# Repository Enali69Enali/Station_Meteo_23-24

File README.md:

# Station_Meteo_23-24
## Description du projet
Pour le cours de projet d'électronique lors de la 4e année du cycle d'ingénieur en alternance, celui ci réalise une girouette pour la station météo d'une ruche connectée. 
Une girouette est un objet de mesure pour nous donner la direction du vent. Ce projet reprend le projet Github 2022-2023 : [Station_Meteo_2022-2023](https://github.com/Solene49000/Station_Meteo_2022-2023). 
Dans ce projet, leur systeme de girouette n'était pas fonctionnelle, du à des differences de tensions trop faible par rapport au différente position de la fleche de la girouette. Nous proposons donc une solution alternative à ce probleme avec notre projet. 

Ce projet de station météo comporte plusieurs composants tels que:
- La quantité de pluie tombée 
- La vitesse du vent 
- La luminosité
- La température 
- L'humidité
Mais nous nous concentrons surtout sur la direction du vent avec la girouette. 

Pour voir la présentation du projet en cours, cliquez [ici](https://github.com/Enali69Enali/Station_Meteo_23-24/blob/master/rapport_de_s%C3%A9ance/Premier%20pr%C3%A9sentation%20%C3%A9lectronique.pdf).

## Fonctionnement
La première question à laquelle nous avons du repondre est : **Comment connaitre la direction de vent sans utilisé la premiere méthode ?** 
Le difference de tension est une bonne méthode mais devait etre plus importante pour faire fonctionner le projet. 
Nous sommes donc partis sur une idée de CODE GRAY (1 bit se change à la fois) avec 4 entrée. Pour avoir une seule sortie nous avons utilisé un réseau R2R.
### Le projet physique
Pour simuler le CODE GRAY, nous avons pensé à une idée de LED émettrices et photo-transitors récepteurs séparer par un tourniquet fait en impression 3D. Quand il y aura le passage d'un trou (pas de matiere), les photo-transitor recevront la lumière infrarouge. Sinon rien ne sera perçu.
Voici les principales impressions 3D nécessaire pour le projet :
* [Boite maintenant le PCB](https://github.com/Enali69Enali/Station_Meteo_23-24/blob/master/modelisation_3D/boite.stl) (Attention dans le fichier .stl il manque un trou pour faire passer les câbles que nous avons rajoutés en en faisant un dans le fond de la boite avec un fer à souder. Pour les autres modifications regarder [ici](#petits-défaut-à-améliorer-pour-le-bon-fonctionnement-du-projet))
* [Couvercle](https://github.com/Enali69Enali/Station_Meteo_23-24/blob/master/modelisation_3D/cylindre%20led-couvercle.stl) (Attention le PCB a un sens sinon celui ci ne passera pas avec le couvercle)
* [Réajusteur pour le roulement](https://github.com/Enali69Enali/Station_Meteo_23-24/blob/master/modelisation_3D/calle%20roulement.stl)
* Fleche de la girouette nous avait été déja fournis

Pour le montage, il suffit de collé le réajusteur pour le roulement sur la tige de la boite, puis de placé un roulement adapté pour emboité le couvecle et la boite. Les impressions sont fait pour des roulements aux dimensions de : diamètre extérieur 22mm, diamètre intérieur 8mm et diamètre de hauteur 7mm.

En plus a été designé un cache pour séparer LEDs/ photo-transistors les uns des autres (voir [le rapport du jour 13/03 de PELLETIER](https://github.com/Enali69Enali/Station_Meteo_23-24/blob/master/rapport_de_s%C3%A9ance/Rapport13_03_2024PELLETIER.pdf)). Ceux ci n'ont pas encore été testé.

### Le projet électronique
#### Hardware
Le [PCB](https://github.com/Enali69Enali/Station_Meteo_23-24/blob/master/BoardsEAGLE/R2R_v2.1.brd) contenant le réseau R2R doit être imprimés (si vous ne l'avez pas déjà) et ajouté avec chaque composant.
Pour les LEDs et photo-transistors il faut que ceux ci soit soudé au dos de la carte avec la tete reposant sur le plastique du PCB pour être à la même hauteur tous, pour le passage dans le tourniquet soit synchronisé. 
Les LED et phototransistors travaillent sur la même longueur d'onde, cad 940 nm (infrarouge). Les phototransistors sont utilisés en emmeteur commun avec un inverseur MOS à sa sortie afin d'avoir réellement 0 ou 3.3V et pas de valeurs entre pour le bon fonctionnement du réseau R2R. L'angle de réception des phototransistors a été choisi le plus petit possible (et disponible), cad 28º, afin de limiter le plus possible les parasites des autre leds.

#### Software
Un fois téléversé, le programme rentre en light sleep et se réveille toute les 15 secondes (ou si reception d'une goutte de pluie), ce
qui permet d'obtenir la position de la girouette
Il y a 16 position differentes, Ouest etant la plus petite, tous les phototransistors recevant tous de la lumière et Nord etant la plus grande, tous les transistors etant cachés.
Actuellement, le valeurs sont complètement à refaire: la courbe n'étant pas linéaire et les valeurs ayant été déterminées avec le PCB de test, les écarts entre les valeurs sont trop grand et les résultats étaient au final mieux que prévu.
Le code de la girouette reste extrêmement simple, etant juste un else-if

## Installation
Préparer le modèle de la girouette physique avec le PCB à l'intérieur.
Il faut brancher le cable micro USB à l'ordinateur pour pouvoir téléverser le code mais voir aussi les informations envoyées par la girouette
Ensuite il faut alimenter la girouette en 3.3V: le fil rouge doit être branché au 3.3V et le fil noir au GND.
Pour vérifier que le montage fonctionne bien, environs 170 mA sont "consommés" par notre montage et sont donc visible sur le générateur
de tension

## Utilisation
Nous avons decidé pour nos tests que le N serait pointé à la position 0 0 0 0 (tous les phototransistors ne recoivent pas de rayonnement des LEDs).
Lors du lancement du programme, celui ci retournera toutes les 15 secondes la direction de la girouette. Le projet n'a pas encore été testé en rajoutant l'anémomètre.

## Petits défaut à améliorer pour le bon fonctionnement du projet
- Les calles du PCB dans la boite ne sont pas exactement aligné, il faut la bloqué avec du scotch en exemple et la surélever pour que les LEDs/photo-transistors soient au niveau des trous pour laisser le passage des rayons. Conseil : si vous voulez résoudre ce soucis avant l'impression de la boite, vous devez surélever le fond de la boite de 2-3 mm;
- Les valeurs theoriques recues par la carte sont différentes de la réalité, il faut donc réajuster les valeurs pour la bonne gestion de la direction de la girouette;
- Les séparateurs peuvent être imprimés si ils y a trop d'interférence.

## Auteurs et remerciments
Projet réalisé par DUEE-MOREAU Arwen et PELLETIER Ilane en classe ELSE4 cursus Polytech FISA 4 année sur le semestre 7 et 8 avec l'aide du professeur PETER Christian.

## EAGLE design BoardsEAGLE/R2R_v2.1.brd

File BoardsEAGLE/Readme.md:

Ici sont stockées les dessin cartes (schematics, boards).

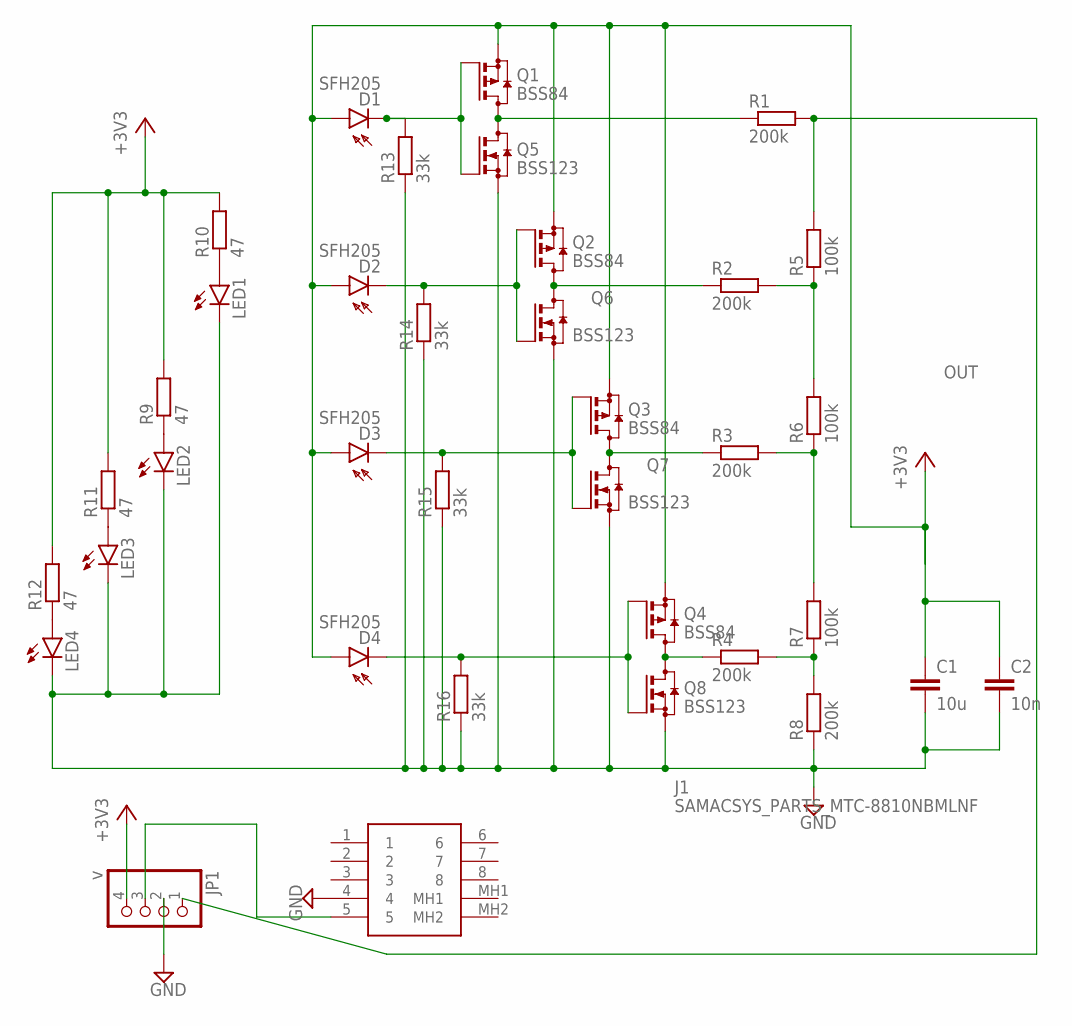
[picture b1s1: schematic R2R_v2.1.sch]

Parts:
C1: 10u; C0805
C2: 10n; C0805
D1, D2, D3, D4: SFH205
J1: SAMACSYS_PARTS_MTC-8810NBMLNF; SAMACSYS_PARTS_MTC8810NBMLNF
JP1: v; 1X04
LED1, LED2, LED3, LED4: LED3MM
Q1, Q2, Q3, Q4: BSS84; SOT23
Q5, Q6, Q7, Q8: BSS123; SOT23
R1, R2, R3, R4, R8: 200k; R1206
R5, R6, R7: 100k; R1206
R9, R10, R11, R12: 47; R1206
R13, R14, R15, R16: 33k; R1206

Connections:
+3V3: C1.1, C2.1, D1.A, D2.A, D3.A, D4.A, JP1.4, Q1.2 (S), Q2.2 (S), Q3.2 (S), Q4.2 (S), R9.2, R10.2, R11.2, R12.2
GND: C1.2, C2.2, J1.4, JP1.2, LED1.K (C), LED2.K (C), LED3.K (C), LED4.K (C), Q5.2 (S), Q6.2 (S), Q7.2 (S), Q8.2 (S), R8.1, R13.1, R14.1, R15.1, R16.1
unnamed: Q1.3 (D), Q5.3 (D), R1.1
unnamed: R2.2, R5.1, R6.2
unnamed: R3.2, R6.1, R7.2
unnamed: R4.2, R7.1, R8.2
unnamed: D4.K (C), Q4.1 (G), Q8.1 (G), R16.2
unnamed: Q3.3 (D), Q7.3 (D), R3.1
unnamed: D2.K (C), Q2.1 (G), Q6.1 (G), R14.2
unnamed: D1.K (C), Q1.1 (G), Q5.1 (G), R13.2
unnamed: LED1.A, R10.1
unnamed: LED2.A, R9.1
unnamed: LED3.A, R11.1
unnamed: LED4.A, R12.1
unnamed: Q2.3 (D), Q6.3 (D), R2.1
unnamed: J1.5, JP1.3
unnamed: D3.K (C), Q3.1 (G), Q7.1 (G), R15.2
unnamed: Q4.3 (D), Q8.3 (D), R4.1
OUT: JP1.1, R1.2, R5.2

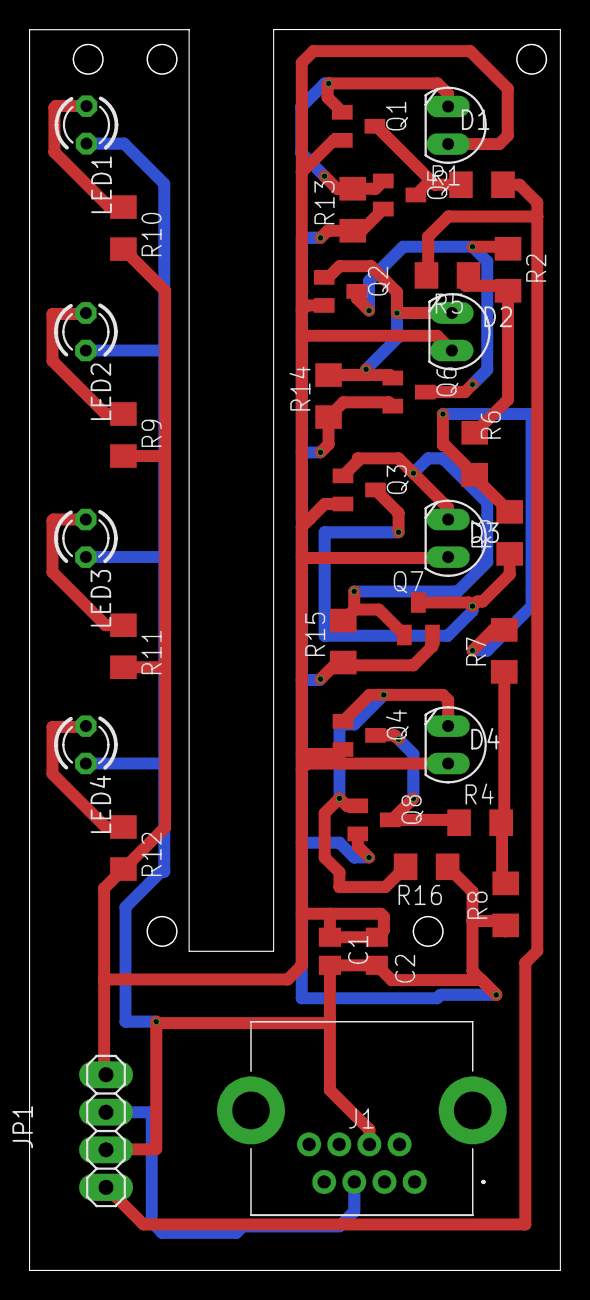
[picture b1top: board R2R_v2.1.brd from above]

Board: 2 copper layers, 35.8 x 83.8 mm, 36 parts (0 on the bottom side), 19 nets.

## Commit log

2023-10-27 ADD A REPOSITORY : rapport de séance
2023-10-27 Ajout du rapport de seance du 27 oct 2023
2023-11-06 Create a directory for 3D models Add v1 GRAY_code_model stl file
2023-11-06 Create Rapport6_11_2023DUEEMOREAU
2023-11-06 Ajout de la version V2 du plateau de la girouette.
2023-11-06 Ajout du rapport de seance du 6 nov 2023
2023-11-20 Create Rapport20_11_2023DUEEMOREAU
2023-11-20 Add files via upload
    Ajout du rapport de seance du 20 11 2023
2023-12-04 Rename Rapport6_11_2023DUEEMOREAU to Rapport06_11_2023DUEEMOREAU
2024-02-13 Create Rapport13_02_2024DUEEMOREAU
2024-02-14 Rapport14_02_2024DUEEMOREAU
2024-02-16 Add last .stl
2024-02-16 Create Rapport16_02_2024DUEEMOREAU
2024-03-02 Create Rapport28_02_2024DUEEMOREAU
2024-03-13 Add files via upload
    Use by factory to generate the R2R PCB
2024-03-14 Create Rapport13_03_2024DUEEMOREAU
2024-03-19 Create Rapport19_03_2024DUEEMOREAU
2024-03-20 Create Rapport20_03_2024DUEEMOREAU
2024-04-03 Create Rapport03_04_2024DUEEMOREAU
